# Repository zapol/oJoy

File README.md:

oJoy
====

Open joystick interface

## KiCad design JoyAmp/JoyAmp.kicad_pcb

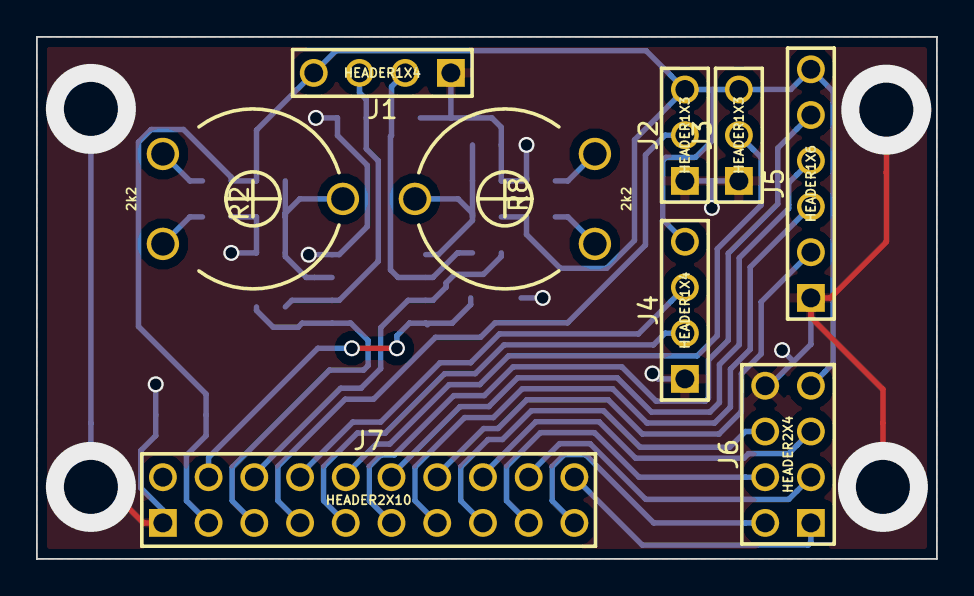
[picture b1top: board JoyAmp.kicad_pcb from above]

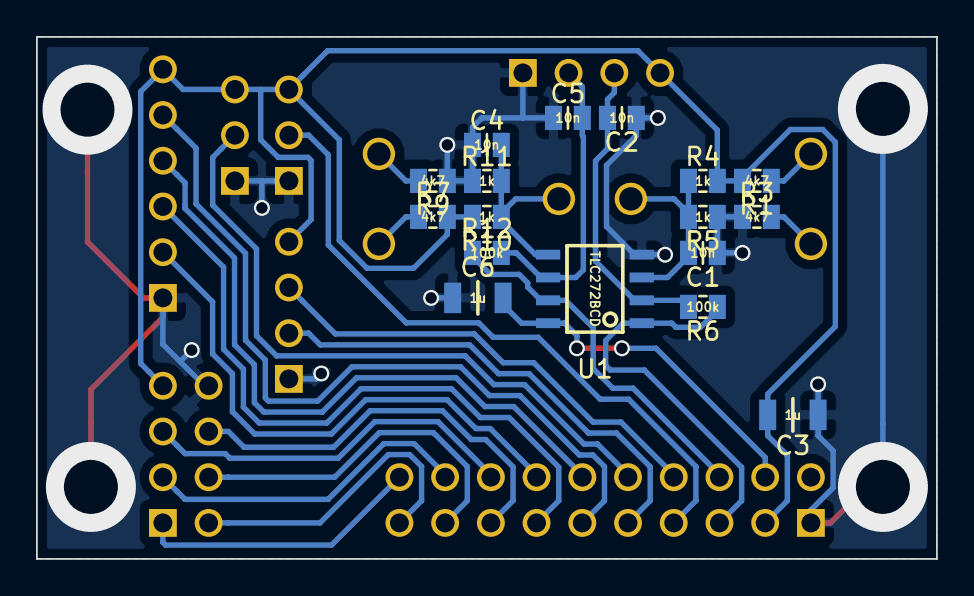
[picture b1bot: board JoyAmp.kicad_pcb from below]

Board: 2 copper layers, 50.0 x 29.0 mm, 26 parts (17 on the bottom side), 27 nets.

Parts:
C1, C2, C4, C5: 10n; C0805
C3, C6: 1u; C1206_L
J1, J4: HEADER1X4; HEADER1x4V
J2, J3: HEADER1X3; HEADER1x3V
J5: HEADER1X6; HEADER1x6V
J6: HEADER2X4; HEADER2x4V
J7: HEADER2X10; HEADER2x10V
R1, R3, R7, R9: 4k7; R0805
R2, R8: 2k2; POT_TRIM_H_10mm
R4, R5, R10, R11: 1k; R0805
R6, R12: 100k; R0805
U1: TLC272BCD; SO8_L

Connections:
+3V3: C3.2, J1.4, J2.3, J3.3, J4.4, J5.6, J6.7, J7.3, R1.2, R4.2, R7.2, R10.2
+5V: C6.2, J7.4, U1.8
/IN1: C2.2, J1.3, R6.2, U1.2
/IN2: C5.2, J1.2, R12.2, U1.6
/IN3: J2.2, J7.7
/IN4: J4.3, J7.8
/IN5: J4.2, J7.9
/IN6: J3.2, J7.10
/IN7: J5.5, J7.11
/IN8: J5.4, J7.12
/IN9: J5.3, J7.13
/IN10: J5.2, J7.14
/IN11: J6.6, J7.15
/IN12: J6.5, J7.16
/IN13: J6.4, J7.17
/IN14: J6.3, J7.18
/IN15: J6.2, J7.19
/IN16: J6.1, J7.20
/OUT1: J7.5, R6.1, U1.1
/OUT2: J7.6, R12.1, U1.7
GND: C1.1, C2.1, C3.1, C4.1, C5.1, C6.1, J1.1, J2.1, J3.1, J4.1, J5.1, J6.8, J7.1, R3.1, R5.1, R9.1, R11.1, U1.4
unnamed: R1.1, R2.1
unnamed: R2.3, R3.2
unnamed: R8.3, R9.2
unnamed: R7.1, R8.1
unnamed: C4.2, R8.2, R10.1, R11.2, U1.5
unnamed: C1.2, R2.2, R4.1, R5.2, U1.3

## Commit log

2013-06-16 Added files.
2013-06-16 Almost trying to work
2013-06-16 Simple joystick working
2013-12-20 Working 2 axis, rudder and dual throttle
2014-08-03 Added PCB project of tensometer amplifier.
